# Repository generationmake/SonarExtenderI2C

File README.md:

# SonarExtenderI2C
Connect up to four Ultrasonic sensor HC-SR04 via I2C to an Arduino or Raspberry Pi

## Connection

### Ultrasonic sensor connection (CN3-CN6)

| Pin | Function |
|-----|----------|
| 1 | 5V |
| 2 | Trigger |
| 3 | Echo |
| 4 | GND |

### Mikrocontroller connection (P1)

| Pin | Function |
|-----|----------|
| 1 | GND |
| 2 | SCL |
| 3 | SDA |
| 4 | Logic voltage (3V3/ 5V) |
| 5 | Interrupt pin |
| 6 | Ultrasonic sensor voltage (5V) |

## How to use

The sensorboard is based on the 16-bit I2C Expander TCA9535 with the slave address 0x20. There are two operating modes for the device. In the manual mode You can evaluate every sensor on Your own, in the automatic mode, all four sensors are evaluated sequentially and an interrupt is rising when all four sensors are triggered once.

### TCA9535 pinout

| Pin | Function |
|-----|----------|
| P0 | DECODE0 |
| P1 | DECODE1 |
| P2 | DECODE2 |
| P3 | STATUS ECHO |
| P4 | TRIGGER0 |
| P5 | TRIGGER1 |
| P6 | TRIGGER2 |
| P7 | TRIGGER3 |
| P10 | D0 |
| P11 | D1 |
| P12 | D2 |
| P13 | D3 |
| P14 | D4 |
| P15 | D5 |
| P16 | D6 |
| P17 | D7 |

### Manual mode

#### 1. Initiate trigger signal 

Before every manual measurement make sure, that TRIGGER0-TRIGGER3 are low and DECODE0-DECODE2 are smaller than 4 in binary.
In manual mode You can trigger a sensor by setting TRIGGER0-TRIGGER3 high according to which sensors You want to use:

|          | TRIGGER0 | TRIGGER1 | TRIGGER2 | TRIGGER3 |
|----------|----|----|----|----|
| Sensor 0 | H | L | L | L |
| Sensor 1 | L | H | L | L |
| Sensor 2 | L | L | H | L |
| Sensor 3 | L | L | L | H |

#### 2. Wait for measurements to finish

If all measurements are finished STATUS ECHO will go high. Here it is important to wait a minimum of 100ms after triggering the sensor.

#### 3. Evaluate the measurement result

The sensorboard has a 8-bit counter for every sensor, that is started and stopped automatically according to the measurement cycles. You can read the data on D0-D7 by setting DECODE0-DECODE2 to the right counter:

|          | DECODE0 | DECODE1 | DECODE2 |
|----------|----|----|----|
| Sensor 0 | L | L | L |
| Sensor 1 | H | L | L |
| Sensor 2 | L | H | L |
| Sensor 3 | H | H | L |

As the counters are running at a 10kHz frequency and the ultrasonic signal needs 29.4us to travel one centimeter, You can calculate the distance to an object in cm by the following formular: ```distance = 100*countervalue/2/29.4```. The maximum distance is 425cm with an accuracy of 4.25cm.

### Automatic mode

#### Starting and stopping the automatic mode

To start the automatic mode, the DECODE Pins need to be set to binary 4, in any other configuration it will not run.
Then all sensors will be triggered one after another.

#### Evaluating the automatic mode results

If all sensors are triggered, the interrupt pin wil rise and You can evaluate the results like in section 2.) of the manual mode.

#### Pausing the automatic mode

To pause the automatic mode, simply set the DECODE Pins to binary 5. In opposite to binary 4, it won't reset and continue with the next sensor.

## Arduino lib

https://github.com/wuehr1999/SonarExtenderI2C-Library

## Aisler order link

https://aisler.net/jonaswuehr/sandbox/sonar-extender-i2-c

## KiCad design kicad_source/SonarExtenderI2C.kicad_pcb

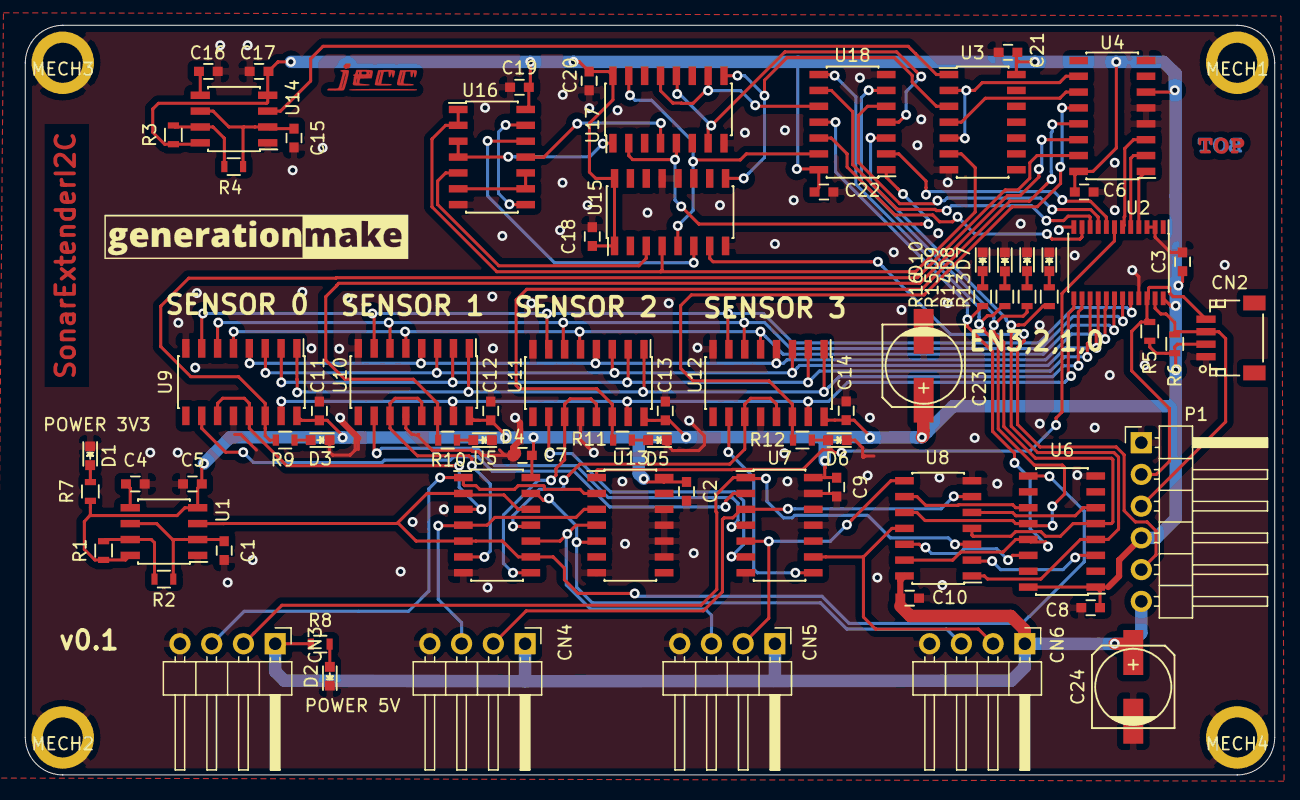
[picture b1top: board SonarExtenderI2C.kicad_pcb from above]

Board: 2 copper layers, 100.0 x 60.0 mm, 82 parts (0 on the bottom side), 82 nets.

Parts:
C1: 1nF; C_0603
C2, C3, C5, C6, C7, C8, C9, C10, C11, C12, C13, C14, C17, C18, C19, C20, C21, C22: 100nF; C_0603
C4, C16: 10nF; C_0603
C15: 1uF; C_0603
C23, C24: 47uF 16V; c_elec_6.3x4.5
CN2: CONN_01X04; Connectors_JST_SM04B-SRSS-TB
CN3, CN4, CN5, CN6: CONN_01X04; PinHeader_1x04_P2.54mm_Horizontal
D1, D2, D3, D4, D5, D6, D7, D8, D9, D10: 150060GS75000; LED_0603
L1: Label; jecc_logo_7.2x2.2
L2: Label; Top
L3: Label; Bot
L4: Label; generationmake_logo
MECH1, MECH2, MECH3, MECH4: MHP_3.2_5.0
P1: CONN_01X06; PinHeader_1x06_P2.54mm_Horizontal
R1, R3: 120k; R_0603
R2, R4: 12k; R_0603
R5, R6: 10k; R_0603
R7, R9, R10, R11, R12, R13, R14, R15, R16: 220; R_0603
R8: 320; R_0603
U1: NE555-IC_logic; SOIC-8_3.9x4.9mm_Pitch1.27mm
U2: TCA9535; TSSOP-24_4.4x7.8mm_Pitch0.65mm
U3, U5, U8: 74xx08; SOIC-14_3.9x8.7mm_Pitch1.27mm
U4: 74xx138-IC_logic; SOIC-16_3.9x9.9mm_Pitch1.27mm
U6: 74xx175-IC_logic; SOIC-16_3.9x9.9mm_Pitch1.27mm
U7: 74xx04-IC_logic; SOIC-14_3.9x8.7mm_Pitch1.27mm
U9, U10, U11, U12: 74xx590-IC_logic; SOIC-16_3.9x9.9mm_Pitch1.27mm
U13: 74xx4002-IC_logic; SOIC-14_3.9x8.7mm_Pitch1.27mm
U14: NE555; SOIC-8_3.9x4.9mm_Pitch1.27mm
U15, U17: 74xx175; SOIC-16_3.9x9.9mm_Pitch1.27mm
U16: 74xx00; SOIC-14_3.9x8.7mm_Pitch1.27mm
U18: 74xx32; SOIC-14_3.9x8.7mm_Pitch1.27mm

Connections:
+3V3: C2.1, C3.1, C5.1, C6.1, C7.1, C8.1, C9.1, C11.1, C12.1, C13.1, C14.1, C17.1, C18.1, C19.1, C20.1, C21.1, C22.1, C23.1, CN2.2, P1.4, R1.1, R3.1, R5.1, R6.1, R7.1, U1.4, U1.8, U2.24, U3.14, U4.6, U4.16, U5.14, U6.1, U6.16, U7.14, U9.16, U10.16, U11.16, U12.16, U13.14, U14.4, U14.8, U15.1, U15.16, U16.14, U17.16, U18.14
+5V: C10.1, C24.1, CN3.1, CN4.1, CN5.1, CN6.1, P1.6, R8.1, U8.14
/CLK_10KHZ: U1.3, U5.2, U5.5, U5.9, U5.12, U6.9
/CLK_ECHO0: U5.3, U9.11, U9.13
/CLK_ECHO1: U5.6, U10.11, U10.13
/CLK_ECHO2: U5.8, U11.11, U11.13
/CLK_ECHO3: U5.11, U12.11, U12.13
/D0: U2.13, U9.15, U10.15, U11.15, U12.15
/D1: U2.14, U9.1, U10.1, U11.1, U12.1
/D2: U2.15, U9.2, U10.2, U11.2, U12.2
/D3: U2.16, U9.3, U10.3, U11.3, U12.3
/D4: U2.17, U9.4, U10.4, U11.4, U12.4
/D5: U2.18, U9.5, U10.5, U11.5, U12.5
/D6: U2.19, U9.6, U10.6, U11.6, U12.6
/D7: U2.20, U9.7, U10.7, U11.7, U12.7
/DECODE0: U2.4, U4.1
/DECODE1: U2.5, U4.2
/DECODE2: U2.6, U4.3
/ECHO0: CN3.3, U5.1, U13.2
/ECHO1: CN4.3, U5.4, U13.3
/ECHO2: CN5.3, U5.10, U13.4
/ECHO3: CN6.3, U5.13, U13.5
/I2C_SCL: CN2.4, P1.2, R5.2, U2.22
/I2C_SDA: CN2.3, P1.3, R6.2, U2.23
/RESET0: U7.2, U9.10
/RESET1: U7.4, U10.10
/RESET2: U7.6, U11.10
/RESET3: U7.8, U12.10
/STATUS_ECHO: U2.7, U13.1
/TRIG0: CN3.2, U7.1, U8.3
/TRIG1: CN4.2, U7.3, U8.6
/TRIG2: CN5.2, U7.5, U8.8
/TRIG3: CN6.2, U7.9, U8.11
/auto/AUTOEN: U3.6, U15.4, U16.1, U16.2
/auto/CLK_10Hz: U3.3, U15.9, U17.9
/auto/E0: U17.2, U17.5, U18.1
/auto/E1: U17.7, U17.12, U18.4
/auto/E2: U17.10, U17.13, U18.10
/auto/E3: U15.5, U17.15, U18.13
AUTO: U3.4, U4.11
EN0: R13.1, U6.4, U8.1, U18.3
EN1: R14.1, U6.5, U8.4, U18.6
EN2: R15.1, U6.12, U8.10, U18.8
EN3: R16.1, U6.13, U8.13, U18.11
ENABLE0: R9.1, U4.15, U9.14
ENABLE1: R10.1, U4.14, U10.14
ENABLE2: R11.1, U4.13, U11.14
ENABLE3: R12.1, U4.12, U12.14
GND: C1.2, C2.2, C3.2, C4.2, C5.2, C6.2, C7.2, C8.2, C9.2, C10.2, C11.2, C12.2, C13.2, C14.2, C15.2, C16.2, C17.2, C18.2, C19.2, C20.2, C21.2, C22.2, C23.2, C24.2, CN2.1, CN3.4, CN4.4, CN5.4, CN6.4, D1.1, D2.1, D3.1, D4.1, D5.1, D6.1, D7.1, D8.1, D9.1, D10.1, MECH1.1, MECH2.1, MECH3.1, MECH4.1, P1.1, U1.1, U2.2, U2.3, U2.12, U2.21, U3.7, U4.4, U4.5, U4.8, U5.7, U6.8, U7.7, U7.11, U7.13, U8.7, U9.8, U9.12, U10.8, U10.12, U11.8, U11.12, U12.8, U12.12, U13.7, U13.9, U13.10, U13.11, U13.12, U14.1, U15.8, U15.12, U15.13, U16.7, U17.8, U18.7
I2C_INT: P1.5, U15.7
unnamed: C1.1, R2.2, U1.2, U1.6
unnamed: C4.1, U1.5
unnamed: C15.1, R4.2, U14.2, U14.6
unnamed: C16.1, U14.5
unnamed: D1.2, R7.2
unnamed: D2.2, R8.2
unnamed: D3.2, R9.2
unnamed: D4.2, R10.2
unnamed: D5.2, R11.2
unnamed: D6.2, R12.2
unnamed: D7.2, R13.2
unnamed: D8.2, R14.2
unnamed: D9.2, R15.2
unnamed: D10.2, R16.2
unnamed: R1.2, R2.1, U1.7
unnamed: R3.2, R4.1, U14.7
unnamed: U6.3, U8.2
unnamed: U6.6, U8.5
unnamed: U6.11, U8.9
unnamed: U6.14, U8.12
unnamed: U3.1, U14.3
unnamed: U15.3, U16.5
unnamed: U15.6, U16.12
unnamed: U16.3, U16.4, U17.1
unnamed: U16.6, U16.9, U16.10
unnamed: U16.11, U17.4
unnamed: U16.8, U16.13
PAUSE: U3.2, U3.5, U4.10
T0: U2.8, U18.2
T1: U2.9, U18.5
T2: U2.10, U18.9
T3: U2.11, U18.12

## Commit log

2020-05-31 added first comments
2020-05-31 updated formatting
2020-06-01 added first draft of schematic
2020-06-01 added auto measure circuit and echo status
2020-06-01 added short description
2020-06-01 added ground/ 3v3 connections
2020-06-01 added logic table for auto evaluation
2020-06-01 changed and colorized logic table
2020-06-01 colorized logic table
2020-06-01 centered logic table
2020-06-02 changed logic table
2020-06-07 added connector for I2C, annotated schematic
2020-06-07 assigned footprints to all parts, generated netlist
2020-06-07 exchanged I2C expanders to TCA9535 (16 bit type), generated schematic pdf
2020-06-08 schematic changed
2020-06-10 finished pcb layout
2020-06-13 reacted to review
2020-06-15 added led digikey order numbers
2020-06-22 updated logic table
2020-06-28 added pause mode for automate
2020-06-29 layout changed
2020-07-03 added EN LEDS
2020-07-04 updated schematics pdf
2020-07-05 added doc images
2020-07-05 moved files
2020-07-17 added example code and lib
2020-08-10 autoread callback bugfix
2020-08-16 changed folder structure
2020-08-16 bugfix
2020-08-19 fixed autoreadCallback hangup
2020-08-19 bugfix 2.0
2020-09-17 updated schematics
2020-09-17 solved issues in schematics
2020-09-17 moved software to library repository
2020-09-18 moved lib
